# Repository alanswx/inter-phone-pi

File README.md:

# inter-phone-pi
Adapter to turn an inter-phone into a sip phone

## make sure to setup default audio devices using 
```bash
echo setup audio devices: sudo raspi-config
sudo apt-get install twinkle
sudo rm /usr/lib/python3.11/EXTERNALLY-MANAGED
sudo pip3 install pytwinkle
```

## on one pi, or another computer you will need an asterisk or SIP server

from here:  https://www.dslreports.com/forum/r30661088-PBX-FreePBX-for-the-Raspberry-Pi

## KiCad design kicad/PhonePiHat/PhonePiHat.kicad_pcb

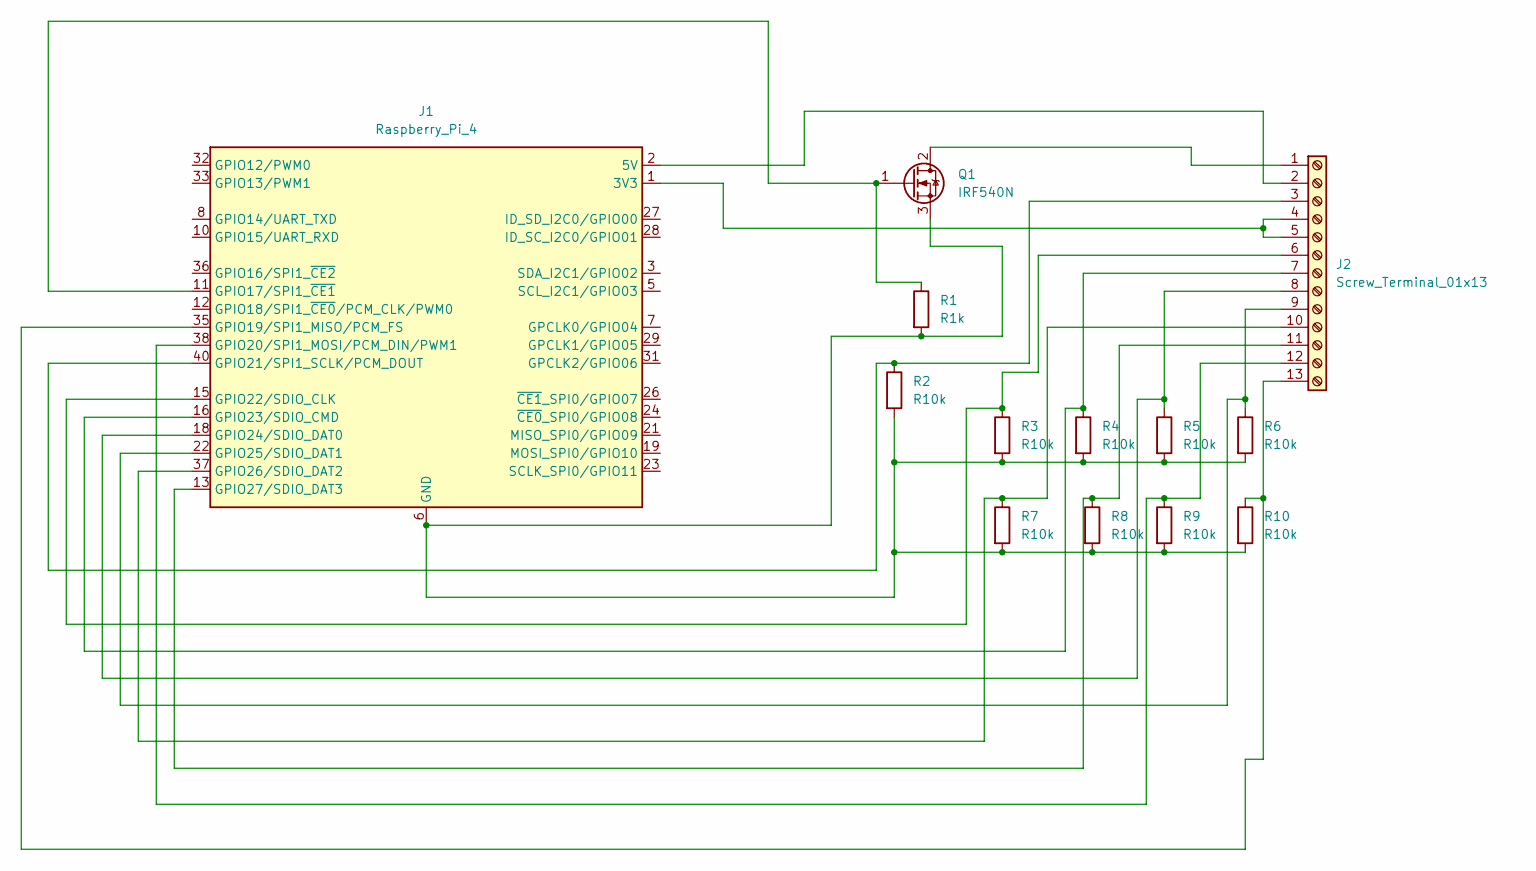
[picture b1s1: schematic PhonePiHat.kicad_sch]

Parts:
J1: Raspberry_Pi_4; Raspberry_Pi_Zero_Socketed_THT_FaceDown_MountingHoles
J2: Screw_Terminal_01x13; TerminalBlock_MaiXu_MX126-5.0-13P_1x13_P5.00mm
Q1: IRF540N; TO-220-3_Vertical
R1: R1k; R_Axial_DIN0204_L3.6mm_D1.6mm_P1.90mm_Vertical
R2: R10k
R3, R4, R5, R6, R7, R8, R9, R10: R10k; R_Axial_DIN0204_L3.6mm_D1.6mm_P1.90mm_Vertical

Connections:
unnamed: J1.11 (GPIO17/SPI1_~CE1), Q1.1 (G), R1.1
unnamed: J1.35 (GPIO19/SPI1_MISO/PCM_FS), J2.13, R10.1
unnamed: J1.38 (GPIO20/SPI1_MOSI/PCM_DIN/PWM1), J2.12, R9.1
unnamed: J1.40 (GPIO21/SPI1_SCLK/PCM_DOUT), J2.3, R2.1
unnamed: J1.15 (GPIO22/SDIO_CLK), J2.6, R3.1
unnamed: J1.16 (GPIO23/SDIO_CMD), J2.7, R4.1
unnamed: J1.18 (GPIO24/SDIO_DAT0), J2.8, R5.1
unnamed: J1.22 (GPIO25/SDIO_DAT1), J2.9, R6.1
unnamed: J1.37 (GPIO26/SDIO_DAT2), J2.10, R7.1
unnamed: J1.13 (GPIO27/SDIO_DAT3), J2.11, R8.1
unnamed: J2.1, Q1.2 (D)
unnamed: J1.2 (5V), J1.4 (5V), J2.2
unnamed: J1.1 (3V3), J1.17 (3V3), J2.4, J2.5
unnamed: J1.6 (GND), J1.9 (GND), J1.14 (GND), J1.20 (GND), J1.25 (GND), J1.30 (GND), J1.34 (GND), J1.39 (GND), Q1.3 (S), R1.2, R2.2, R3.2, R4.2, R5.2, R6.2, R7.2, R8.2, R9.2, R10.2

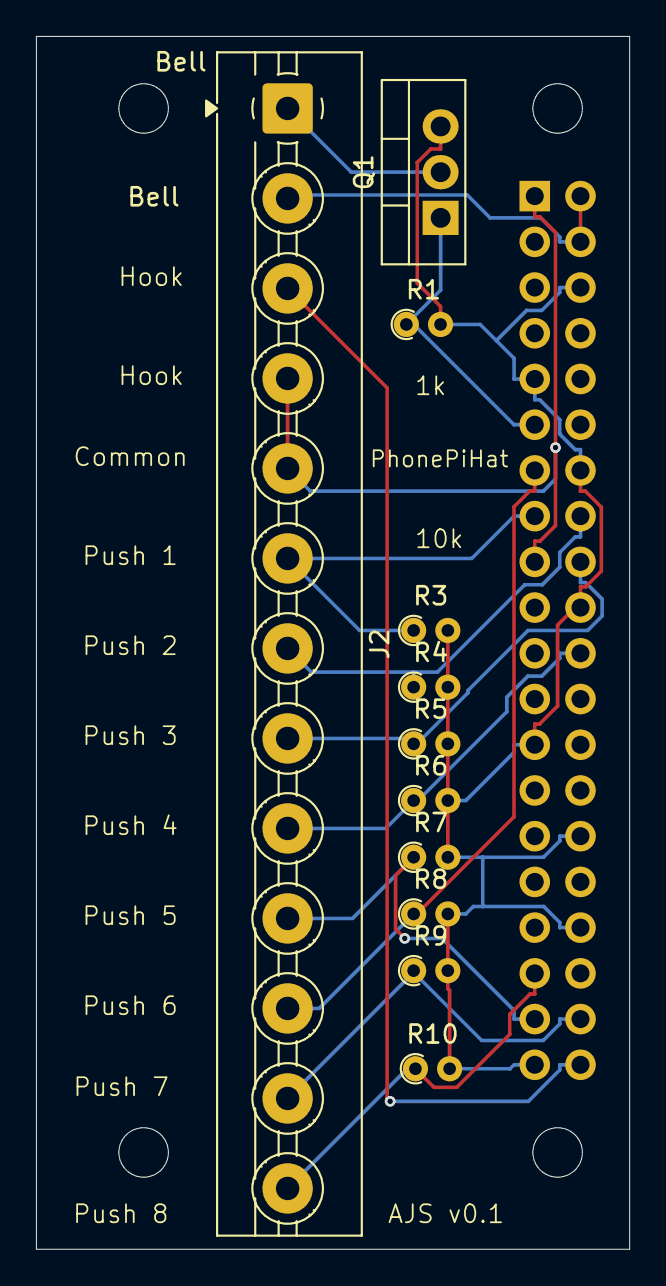
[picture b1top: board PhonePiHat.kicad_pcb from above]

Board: 2 copper layers, 33.0 x 67.4 mm, 12 parts (1 on the bottom side), 14 nets.

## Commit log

2024-04-18 first check in
2024-04-19 fixes to state machine
2024-05-07 added sip server
2025-02-28 added kicad
2025-03-30 v2 board
2025-05-10 added tester
